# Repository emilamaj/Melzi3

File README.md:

# Melzi3
An attempt to update to 32 bits the now deprecated RepRap Melzi control board

Created using KiCAD

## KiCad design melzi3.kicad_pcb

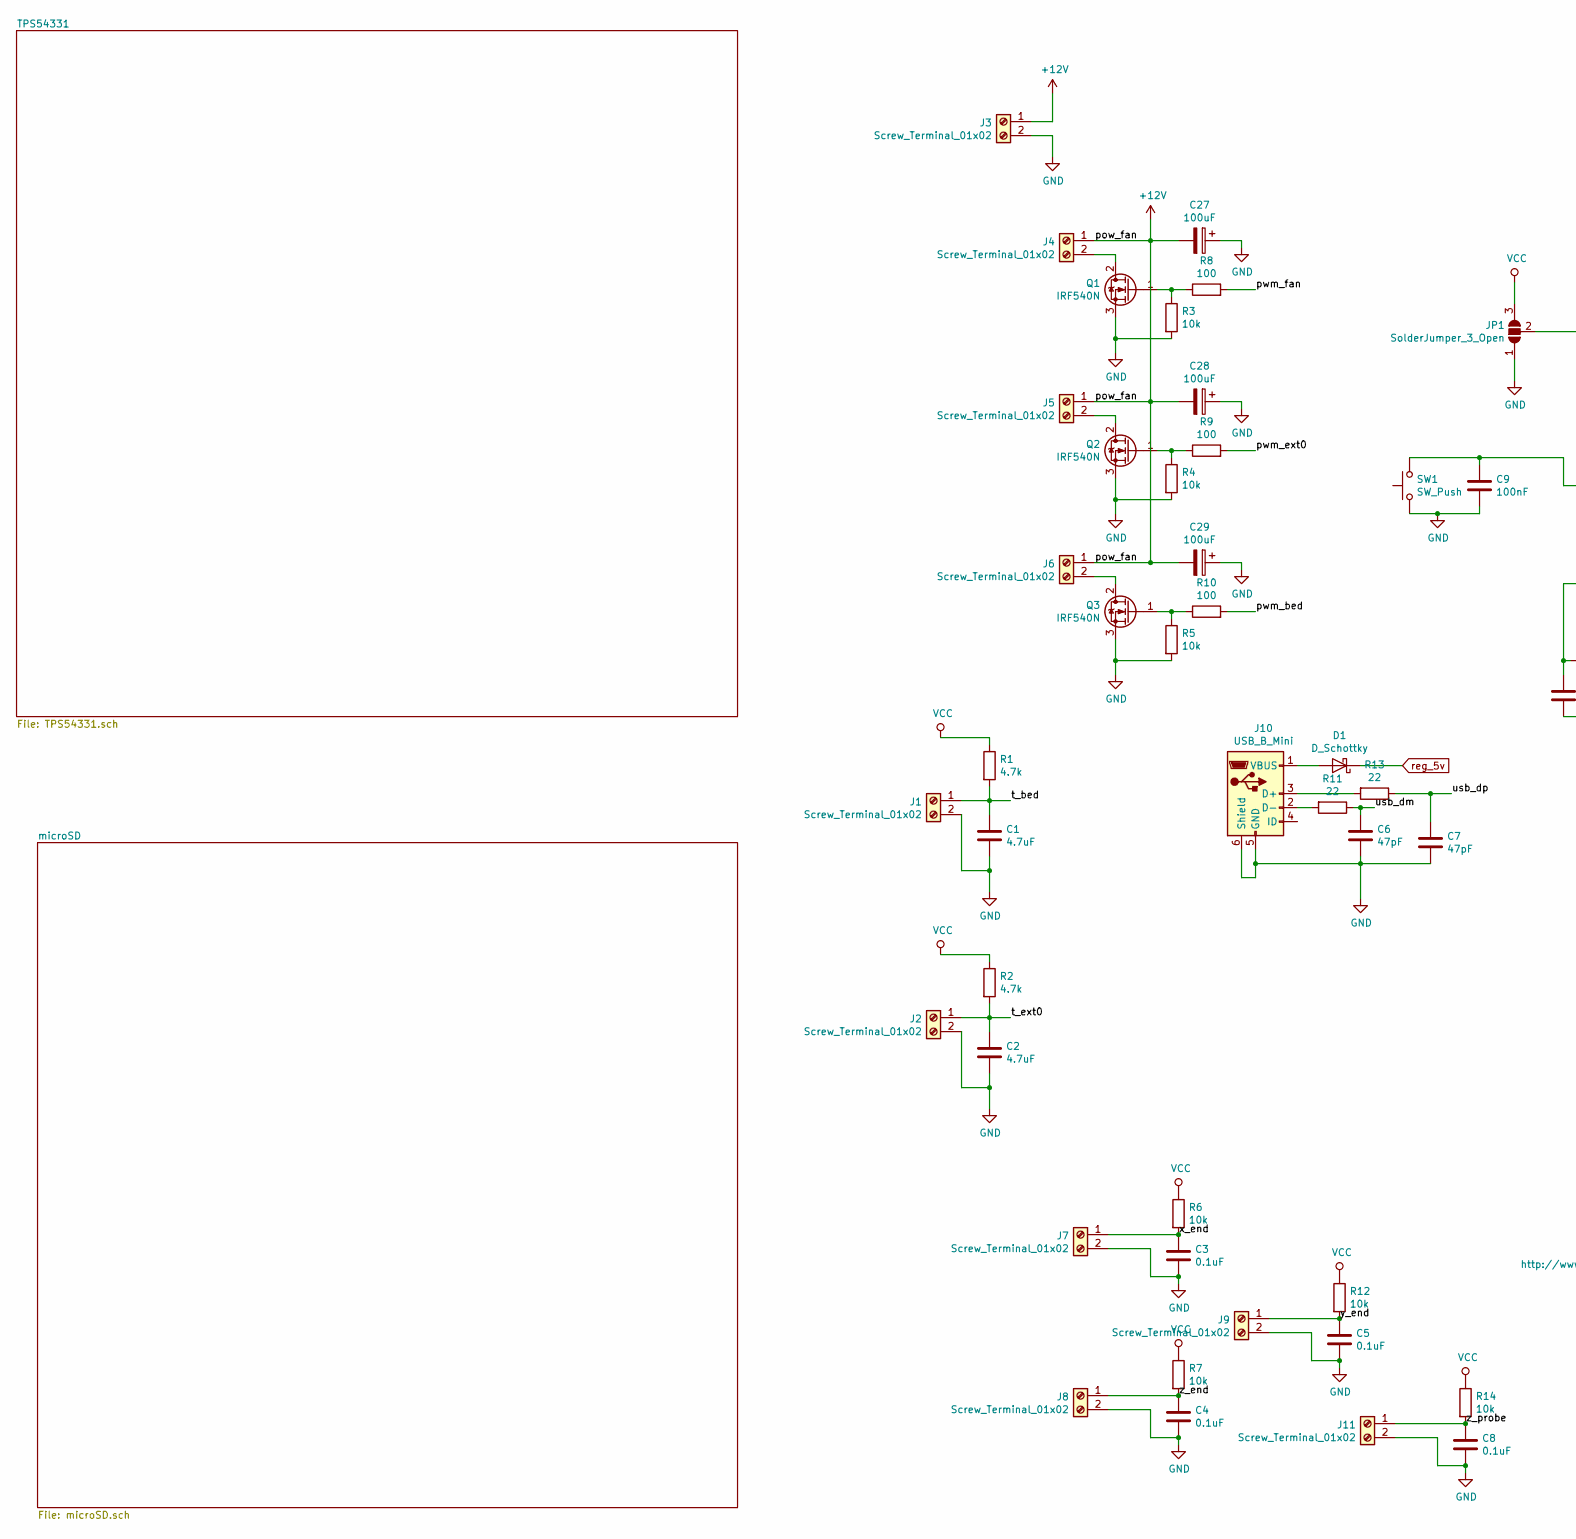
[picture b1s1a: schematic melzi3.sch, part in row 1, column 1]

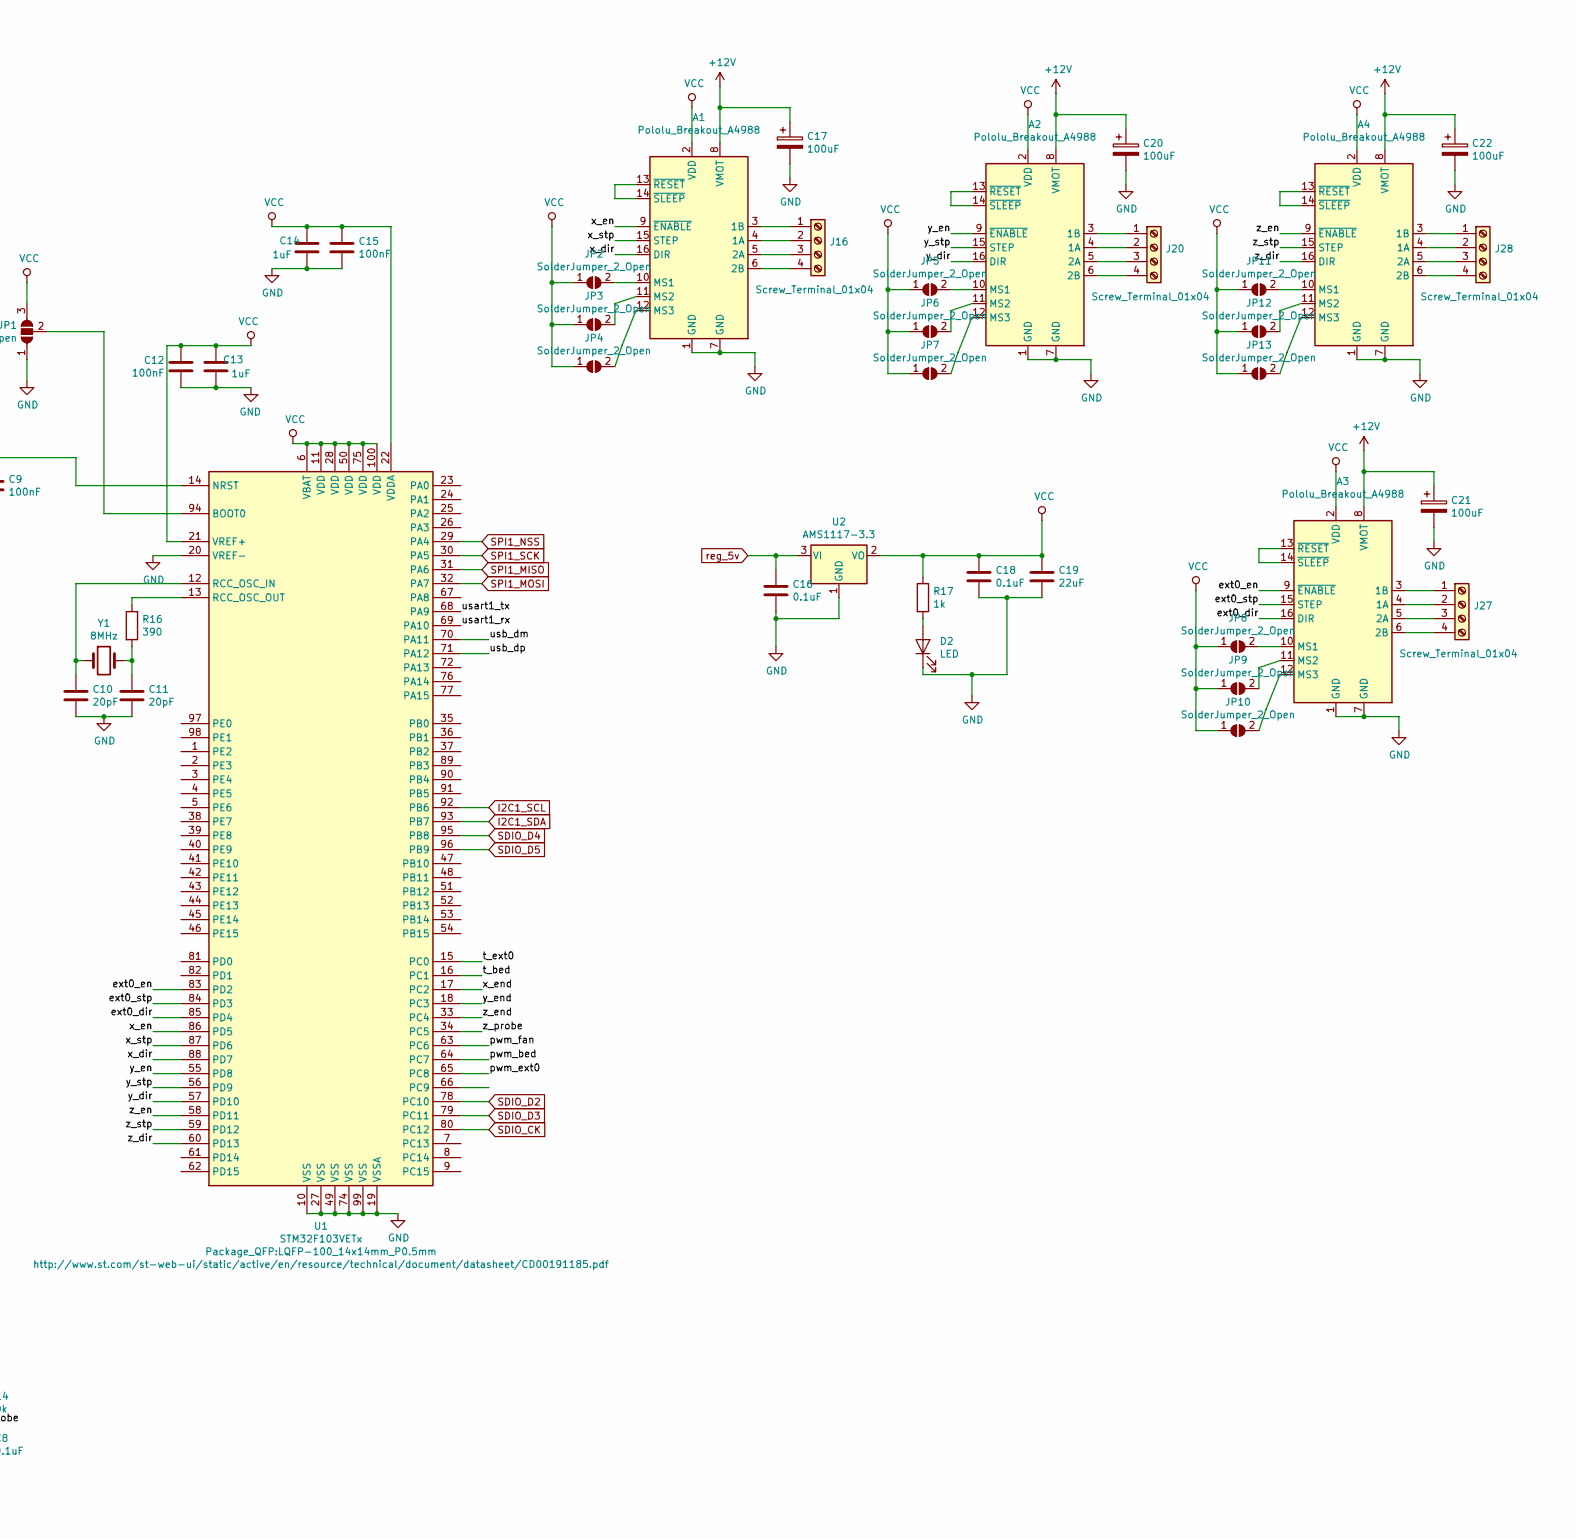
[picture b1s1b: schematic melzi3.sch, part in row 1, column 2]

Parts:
A1, A2, A3, A4: Pololu_Breakout_A4988; Pololu_Breakout-16_15.2x20.3mm
C1, C2: 4.7uF; C_0805_2012Metric
C3, C4, C5, C8, C16, C18: 0.1uF; C_0805_2012Metric
C6, C7: 47pF; C_0603_1608Metric
C9, C12, C15: 100nF; C_0805_2012Metric
C10, C11: 20pF; C_0603_1608Metric
C13, C14: 1uF; C_0805_2012Metric
C17, C20, C21, C22, C27, C28, C29: 100uF; CP_Elec_3x5.3
C19: 22uF; CP_Elec_3x5.3
D1: D_Schottky; D_0805_2012Metric
D2: LED; LED_0603_1608Metric
J1, J2, J3, J4, J5, J6, J7, J8, J9, J11: Screw_Terminal_01x02; TerminalBlock_bornier-2_P5.08mm
J10: USB_B_Mini; USB_Mini-B_Lumberg_2486_01_Horizontal
J16, J20, J27, J28: Screw_Terminal_01x04; TerminalBlock_bornier-4_P5.08mm
JP1: SolderJumper_3_Open; SolderJumper-3_P1.3mm_Open_RoundedPad1.0x1.5mm
JP2, JP3, JP4, JP5, JP6, JP7, JP8, JP9, JP10, JP11, JP12, JP13: SolderJumper_2_Open; SolderJumper-2_P1.3mm_Open_TrianglePad1.0x1.5mm
Q1, Q2, Q3: IRF540N; TO-220-3_Vertical
R1, R2: 4.7k; R_0805_2012Metric
R3, R4, R5, R6, R7, R12, R14: 10k; R_0805_2012Metric
R8, R9, R10: 100; R_0805_2012Metric
R11, R13: 22; R_0805_2012Metric
R16: 390; R_0805_2012Metric
R17: 1k; R_0805_2012Metric
SW1: SW_Push; Panasonic_EVQPUJ_EVQPUA
U1: STM32F103VETx; LQFP-100_14x14mm_P0.5mm
U2: AMS1117-3.3; SOT-223-3_TabPin2
Y1: 8MHz; Crystal_SMD_3215-2Pin_3.2x1.5mm

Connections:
+12V: A1.8 (VMOT), A2.8 (VMOT), A3.8 (VMOT), A4.8 (VMOT), C17.1, C20.1, C21.1, C22.1, C27.2, C28.2, C29.2, J3.1, J4.1, J5.1, J6.1; also elsewhere on the board
/ext0_dir: A3.16 (DIR), U1.85 (PD4)
/ext0_en: A3.9 (~ENABLE), U1.83 (PD2)
/ext0_stp: A3.15 (STEP), U1.84 (PD3)
/pwm_bed: R10.2, U1.64 (PC7)
/pwm_ext0: R9.2, U1.65 (PC8)
/pwm_fan: R8.2, U1.63 (PC6)
/t_bed: C1.1, J1.1, R1.2, U1.16 (PC1)
/t_ext0: C2.1, J2.1, R2.2, U1.15 (PC0)
/usart1_rx: U1.69 (PA10)
/usart1_tx: U1.68 (PA9)
/x_dir: A1.16 (DIR), U1.88 (PD7)
/x_en: A1.9 (~ENABLE), U1.86 (PD5)
/x_end: C3.1, J7.1, R6.2, U1.17 (PC2)
/x_stp: A1.15 (STEP), U1.87 (PD6)
/y_dir: A2.16 (DIR), U1.57 (PD10)
/y_en: A2.9 (~ENABLE), U1.55 (PD8)
/y_end: C5.1, J9.1, R12.2, U1.18 (PC3)
/y_stp: A2.15 (STEP), U1.56 (PD9)
/z_dir: A4.16 (DIR), U1.60 (PD13)
/z_en: A4.9 (~ENABLE), U1.58 (PD11)
/z_end: C4.1, J8.1, R7.2, U1.33 (PC4)
/z_probe: C8.1, J11.1, R14.2, U1.34 (PC5)
/z_stp: A4.15 (STEP), U1.59 (PD12)
GND: A1.1 (GND), A1.7 (GND), A2.1 (GND), A2.7 (GND), A3.1 (GND), A3.7 (GND), A4.1 (GND), A4.7 (GND), C1.2, C2.2, C3.2, C4.2, C5.2, C6.2, C7.2, C8.2, C9.2, C10.2, C11.2, C12.2, C13.2, C14.2, C15.2, C16.2, C17.2, C18.2, C19.2, C20.2, C21.2, C22.2, C27.1, C28.1, C29.1, D2.1 (K), J1.2, J2.2, J3.2, J7.2, J8.2, J9.2, J10.5 (GND), J10.6 (Shield), J11.2, JP1.1 (A), Q1.3 (S), Q2.3 (S), Q3.3 (S), R3.2, R4.2, R5.2, SW1.1, U1.10 (VSS), U1.19 (VSSA), U1.20 (VREF-), U1.27 (VSS), U1.49 (VSS), U1.74 (VSS), U1.99 (VSS), U2.1 (GND); also elsewhere on the board
I2C1_SCL: U1.92 (PB6)
I2C1_SDA: U1.93 (PB7)
unnamed: A1.3 (1B), J16.1
unnamed: A1.4 (1A), J16.2
unnamed: A1.5 (2A), J16.3
unnamed: A1.6 (2B), J16.4
unnamed: A1.10 (MS1), JP2.2 (B)
unnamed: A1.11 (MS2), JP3.2 (B)
unnamed: A1.12 (MS3), JP4.2 (B)
unnamed: A1.13 (~RESET), A1.14 (~SLEEP)
unnamed: A2.3 (1B), J20.1
unnamed: A2.4 (1A), J20.2
unnamed: A2.5 (2A), J20.3
unnamed: A2.6 (2B), J20.4
unnamed: A2.10 (MS1), JP5.2 (B)
unnamed: A2.11 (MS2), JP6.2 (B)
unnamed: A2.12 (MS3), JP7.2 (B)
unnamed: A2.13 (~RESET), A2.14 (~SLEEP)
unnamed: A3.3 (1B), J27.1
unnamed: A3.4 (1A), J27.2
unnamed: A3.5 (2A), J27.3
unnamed: A3.6 (2B), J27.4
unnamed: A3.10 (MS1), JP8.2 (B)
unnamed: A3.11 (MS2), JP9.2 (B)
unnamed: A3.12 (MS3), JP10.2 (B)
unnamed: A3.13 (~RESET), A3.14 (~SLEEP)
unnamed: A4.3 (1B), J28.1
unnamed: A4.4 (1A), J28.2
unnamed: A4.5 (2A), J28.3
unnamed: A4.6 (2B), J28.4
unnamed: A4.10 (MS1), JP11.2 (B)
unnamed: A4.11 (MS2), JP12.2 (B)
unnamed: A4.12 (MS3), JP13.2 (B)
unnamed: A4.13 (~RESET), A4.14 (~SLEEP)
unnamed: C9.1, SW1.2, U1.14 (NRST)
unnamed: C10.1, U1.12 (RCC_OSC_IN), Y1.1
unnamed: C11.1, R16.2, Y1.2
unnamed: D1.2 (A), J10.1 (VBUS)
unnamed: D2.2 (A), R17.2
unnamed: J4.2, Q1.2 (D)
unnamed: J5.2, Q2.2 (D)
unnamed: J6.2, Q3.2 (D)
unnamed: J10.2 (D-), R11.2
unnamed: J10.3 (D+), R13.2
unnamed: JP1.2 (C), U1.94 (BOOT0)
unnamed: Q1.1 (G), R3.1, R8.1
unnamed: Q2.1 (G), R4.1, R9.1
unnamed: Q3.1 (G), R5.1, R10.1
unnamed: R16.1, U1.13 (RCC_OSC_OUT)
SDIO_CK: U1.80 (PC12)
SDIO_D2: U1.78 (PC10)
SDIO_D3: U1.79 (PC11)
SDIO_D4: U1.95 (PB8)
SDIO_D5: U1.96 (PB9)
SPI1_MISO: U1.31 (PA6); also elsewhere on the board
SPI1_MOSI: U1.32 (PA7); also elsewhere on the board
SPI1_NSS: U1.29 (PA4); also elsewhere on the board
SPI1_SCK: U1.30 (PA5); also elsewhere on the board
VCC: A1.2 (VDD), A2.2 (VDD), A3.2 (VDD), A4.2 (VDD), C12.1, C13.1, C14.1, C15.1, C18.1, C19.1, JP1.3 (B), JP2.1 (A), JP3.1 (A), JP4.1 (A), JP5.1 (A), JP6.1 (A), JP7.1 (A), JP8.1 (A), JP9.1 (A), JP10.1 (A), JP11.1 (A), JP12.1 (A), JP13.1 (A), R1.1, R2.1, R6.1, R7.1, R12.1, R14.1, R17.1, U1.6 (VBAT), U1.11 (VDD), U1.21 (VREF+), U1.22 (VDDA), U1.28 (VDD), U1.50 (VDD), U1.75 (VDD), U1.100 (VDD), U2.2 (VO); also elsewhere on the board
reg_5v: C16.1, D1.1 (K), U2.3 (VI); also elsewhere on the board
usb_dm: C6.1, R11.1, U1.70 (PA11)
usb_dp: C7.1, R13.1, U1.71 (PA12)

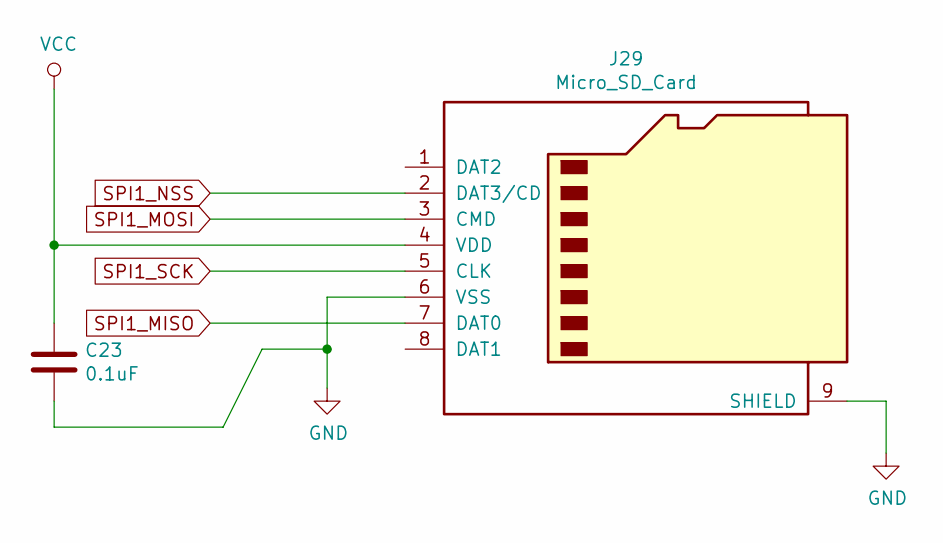
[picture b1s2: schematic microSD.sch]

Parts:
C23: 0.1uF; C_0805_2012Metric
J29: Micro_SD_Card; microSD_HC_Hirose_DM3D-SF

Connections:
GND: C23.2, J29.6 (VSS), J29.9 (SHIELD); also elsewhere on the board
SPI1_MISO: J29.7 (DAT0); also elsewhere on the board
SPI1_MOSI: J29.3 (CMD); also elsewhere on the board
SPI1_NSS: J29.2 (DAT3/CD); also elsewhere on the board
SPI1_SCK: J29.5 (CLK); also elsewhere on the board
VCC: C23.1, J29.4 (VDD); also elsewhere on the board

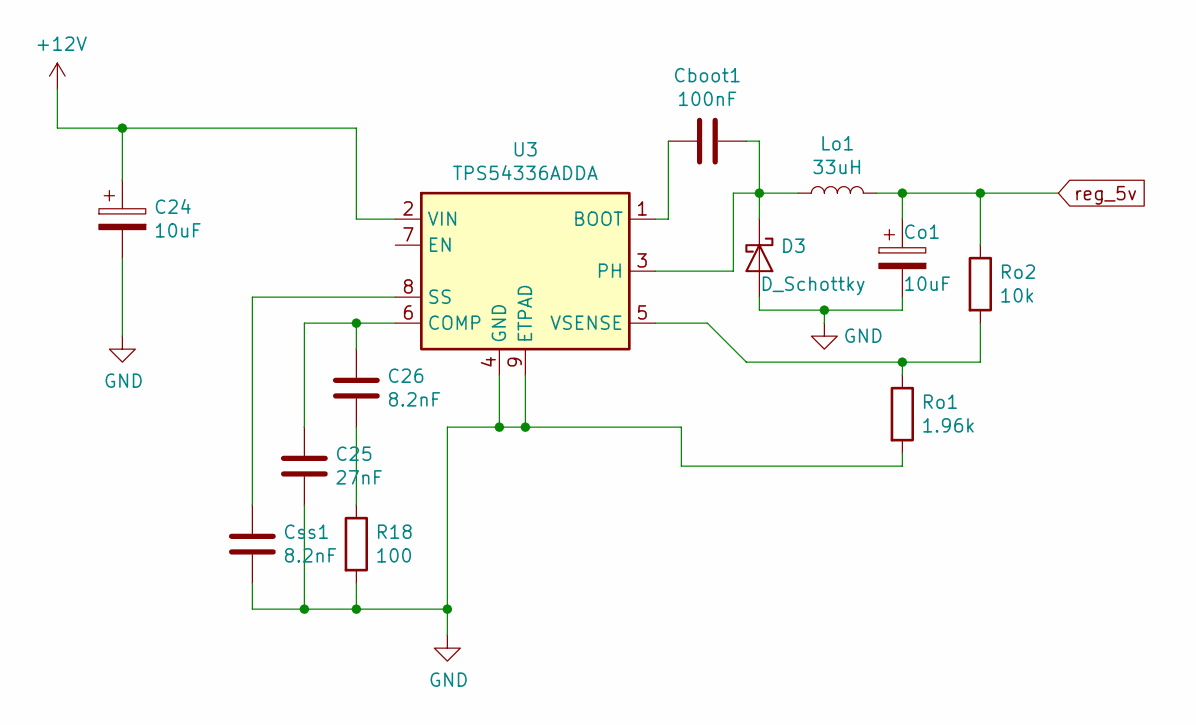
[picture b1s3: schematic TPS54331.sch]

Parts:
C24: 10uF; C_0805_2012Metric
C25: 27nF; C_0805_2012Metric
C26: 8.2nF; C_0805_2012Metric
Cboot1: 100nF; C_0805_2012Metric
Co1: 10uF; CP_Elec_3x5.3
Css1: 8.2nF; C_0805_2012Metric
D3: D_Schottky; D_0805_2012Metric
Lo1: 33uH; L_2816_7142Metric_Pad3.20x4.45mm_HandSolder
R18: 100; R_0805_2012Metric
Ro1: 1.96k; R_0805_2012Metric
Ro2: 10k; R_0805_2012Metric
U3: TPS54336ADDA; TI_SO-PowerPAD-8_ThermalVias

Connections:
+12V: C24.1, U3.2 (VIN); also elsewhere on the board
GND: C24.2, C25.2, Co1.2, Css1.2, D3.2 (A), R18.2, Ro1.2, U3.4 (GND), U3.9 (ETPAD); also elsewhere on the board
unnamed: C25.1, C26.1, U3.6 (COMP)
unnamed: C26.2, R18.1
unnamed: Cboot1.1, D3.1 (K), Lo1.1, U3.3 (PH)
unnamed: Cboot1.2, U3.1 (BOOT)
unnamed: Css1.1, U3.8 (SS)
unnamed: Ro1.1, Ro2.2, U3.5 (VSENSE)
reg_5v: Co1.1, Lo1.2, Ro2.1; also elsewhere on the board

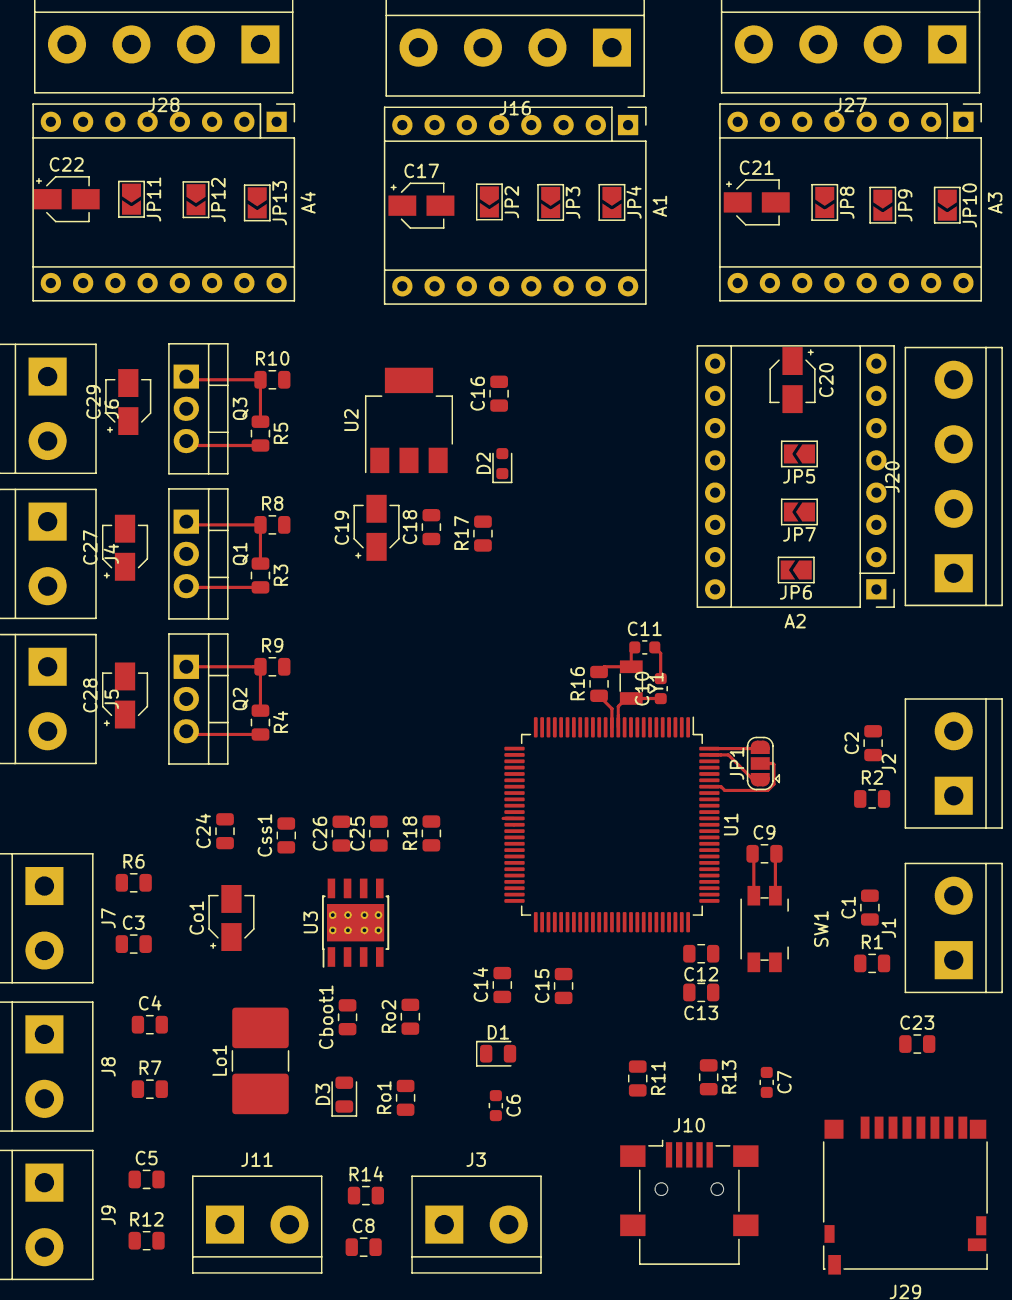
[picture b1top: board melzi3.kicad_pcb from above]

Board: 2 copper layers, 96 parts (0 on the bottom side), 84 nets.
